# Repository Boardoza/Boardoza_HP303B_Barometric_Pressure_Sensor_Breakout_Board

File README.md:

# Boardoza HP303B Barometric Pressure and Temperature Sensor Breakout Board

The **Boardoza HP303B Breakout Board** is a compact and low-power digital **barometric pressure and temperature sensor** designed for applications requiring high accuracy and long-term stability. Based on a **capacitive pressure sensing principle**, the HP303B delivers precise measurements even under changing temperature conditions, making it suitable for demanding environmental sensing tasks.

Each HP303B sensor is **individually calibrated at the factory** and includes a **24-bit internal signal processor** that converts raw sensor data into accurate pressure and temperature values. With support for both **I²C and SPI communication**, an integrated **32-sample FIFO**, and optional **interrupt functionality**, this breakout board is ideal for **IoT devices, wearables, mobile electronics, weather stations, altitude measurement systems, and battery-powered sensor nodes**.

## [Click here to purchase!](https://www.ozdisan.com/p/arduino-sensorleri-ve-modulleri-613/boardoza-hp303b-module-1473941)

| Front Side | Back Side |
|:---:|:---:|
|  |  |

---

## Key Features

- **High-Accuracy Barometric Pressure Sensor:** Designed for precise pressure and altitude measurements across a wide operating range.
- **Integrated Temperature Measurement:** Provides accurate ambient temperature data alongside pressure readings.
- **Factory-Calibrated Sensor:** Each HP303B device is individually calibrated, ensuring reliable and consistent output.
- **Dual Communication Interface:** Supports both **I²C** and **SPI** interfaces for flexible system integration.
- **32-Sample FIFO Buffer:** Reduces host processor load by minimizing frequent data polling.
- **Low Power Consumption:** Optimized for battery-powered and low-energy applications such as wearables and IoT nodes.
- **Interrupt Support:** Optional interrupt signaling via the SDO pin for efficient event-driven designs.

---

## Technical Specifications

**Model:** HP303B  
**Manufacturer:** Boardoza   
**Manufacturer IC:** HOPERF  
**Functions:** Digital Barometric Pressure and Temperature Sensor  
**Supply Voltage:** 3.3 V – 5 V  
**Interface:** I²C, SPI  
**Pressure Measurement Range:** 300 hPa – 1200 hPa  
**Pressure Precision:** ±0.005 hPa (high precision mode)  
**Relative Accuracy:** ±0.06 hPa  
**Absolute Accuracy:** ±1 hPa  
**Temperature Accuracy:** ±0.5 °C  
**Pressure Temperature Sensitivity:** 0.5 Pa/K  
**Measurement Time:**  
- Typical: 27.6 ms (standard mode, 16x)  
- Minimum: 3.6 ms (low precision mode)  
  
**Average Current Consumption:**  
- Pressure Measurement: 1.7 µA @ 1 Hz  
- Temperature Measurement: 1.5 µA @ 1 Hz  
- Standby Mode: 0.5 µA

**FIFO Buffer Depth:** 32 samples  
**Operating Temperature:** -40 °C to +85 °C  
**Board Dimensions:** 20 mm x 20 mm

---

## Board Pinout

### **( J1 ) Main Connector**

| Pin Number | Pin Name | Description |
|:---:|:---:|---|
| 1 | 3V3-5V | Positive Power Supply |
| 2 | SDO | I²C: Address LSB / Interrupt<br>SPI: MISO / Interrupt |
| 3 | CSB | I²C: Not used (leave open)<br>SPI: Chip Select |
| 4 | SDA | I²C: Serial Data<br>SPI: MOSI (4-wire) / Data (3-wire) |
| 5 | SCL | I²C: Serial Clock<br>SPI: Serial Clock |
| 6 | GND | Ground |

### **Jumper Configuration**

| Jumper | Description |
|------|------------|
| JP1, JP2 | SPI mode: Open (default)<br>I²C mode: Short |
| JP3 | I²C Address 0x77: Open (default)<br>I²C Address 0x76: Short |

---

## Board Dimensions

---

## Step Files

[Boardoza HP303B.step](./assets/HP303B%20Step.step)

---

## Datasheet

[HP303B Datasheet](./assets/HP303B%20Datasheet.pdf)

---

## Version History

- V1.0.0 – Initial Release

---

## Support

- If you have any questions or need support, please contact **support@boardoza.com**

---

## **License**

This repository contains both hardware and software components:

### **Hardware Design**

[![CC BY-SA 4.0][cc-by-sa-shield]][cc-by-sa]

All hardware design files are licensed under [Creative Commons Attribution-ShareAlike 4.0 International License][cc-by-sa].

[cc-by-sa]: http://creativecommons.org/licenses/by-sa/4.0/
[cc-by-sa-shield]: https://img.shields.io/badge/License-CC%20BY--SA%204.0-lightgrey.svg

### **Software/Firmware**

[![BSD-3-Clause][bsd-shield]][bsd]

All software and firmware are licensed under [BSD 3-Clause License][bsd].

[bsd]: https://opensource.org/licenses/BSD-3-Clause
[bsd-shield]: https://img.shields.io/badge/License-BSD%203--Clause-blue.svg

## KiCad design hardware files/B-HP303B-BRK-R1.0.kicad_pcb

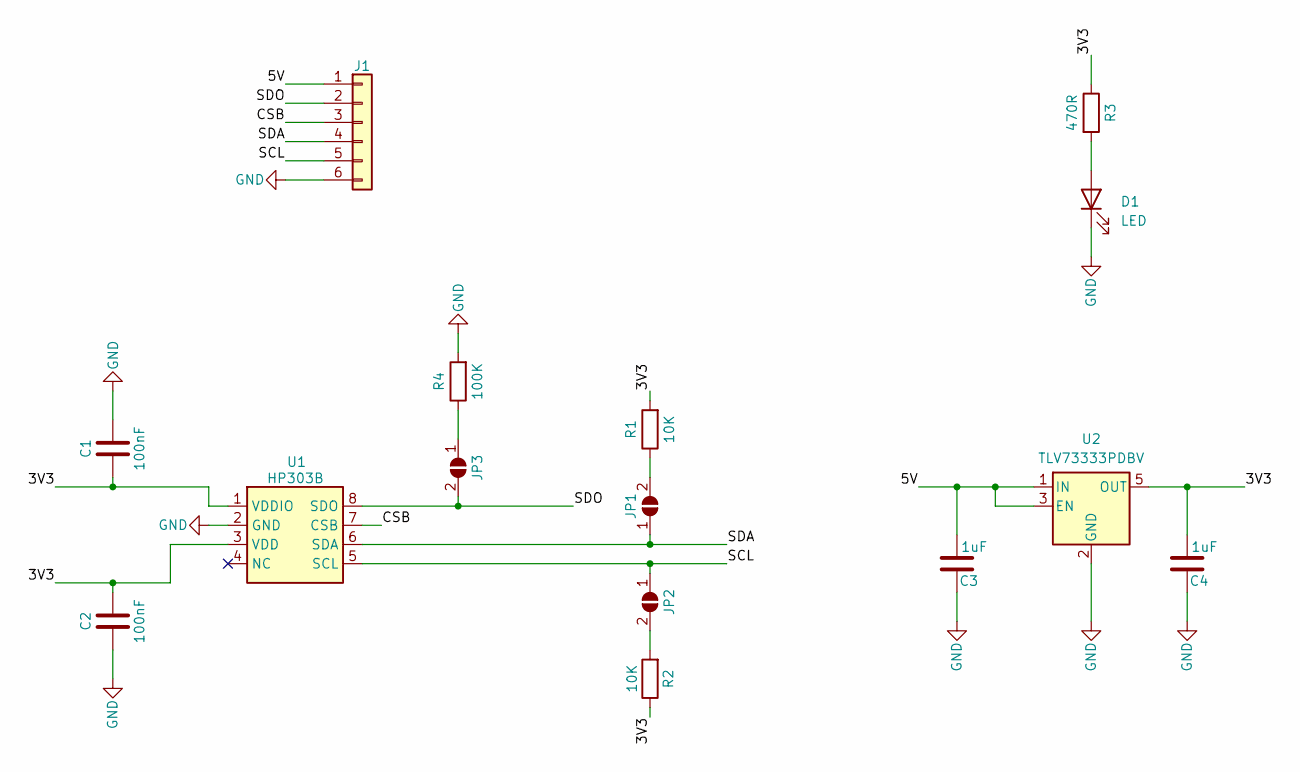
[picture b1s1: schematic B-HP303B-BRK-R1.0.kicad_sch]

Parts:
C1, C2: 100nF; C_0603_1608Metric
C3, C4: 1uF; C_0603_1608Metric
D1: LED; LED_0603_1608Metric
J1: Conn_01x06; 2317-06S_1x06_P2.50mm_Vertical
JP1: SDA; SolderJumper-2_P1.3mm_Open_RoundedPad1.0x1.5mm
JP2: SCK; SolderJumper-2_P1.3mm_Open_RoundedPad1.0x1.5mm
JP3: INT; SolderJumper-2_P1.3mm_Open_RoundedPad1.0x1.5mm
R1, R2: 10K; R_0603_1608Metric
R3: 470R; R_0603_1608Metric
R4: 100K; R_0603_1608Metric
U1: HP303B; MPN HP303B
U2: TLV73333PDBV; SOT-23-5; MPN TLV73333PDBV

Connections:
/3V3: C1.1, C2.2, C4.2, R1.2, R2.1, R3.1, U1.1 (VDDIO), U1.3 (VDD), U2.5 (OUT)
/5V: C3.2, J1.1, U2.1 (IN), U2.3 (EN)
/CSB: J1.3, U1.7 (CSB)
/SCL: J1.5, JP2.1 (A), U1.5 (SCL)
/SDA: J1.4, JP1.1 (A), U1.6 (SDA)
/SDO: J1.2, JP3.2 (B), U1.8 (SDO)
GND: C1.2, C2.1, C3.1, C4.1, D1.1 (K), J1.6, R4.2, U1.2 (GND), U2.2 (GND)
unnamed: D1.2 (A), R3.2
unnamed: JP1.2 (B), R1.1
unnamed: JP2.2 (B), R2.2
unnamed: JP3.1 (A), R4.1

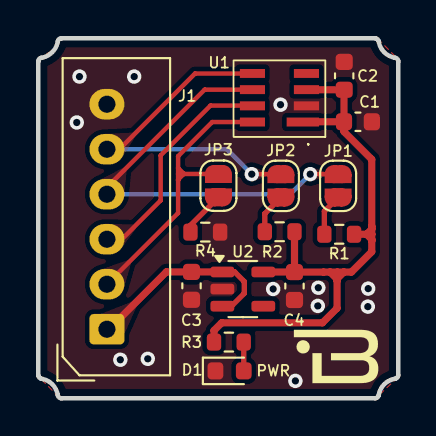
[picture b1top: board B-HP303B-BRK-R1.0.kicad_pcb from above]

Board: 2 copper layers, 20.0 x 20.0 mm, 15 parts (0 on the bottom side), 11 nets.

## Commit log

2026-04-28 Fix comments and improve code clarity
2026-04-28 Fixed comment lines
